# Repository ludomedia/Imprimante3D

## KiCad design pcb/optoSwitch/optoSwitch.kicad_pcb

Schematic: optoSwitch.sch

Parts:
IC1: OPTOSWITCH; DIP4F
K1: CONN_3
R1: 220R
R2: 4k7

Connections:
+5V: K1.1, R1.1, R2.1
GND: IC1.2, IC1.3, K1.3
unnamed: IC1.4, K1.2 (PM), R2.2
unnamed: IC1.1, R1.2

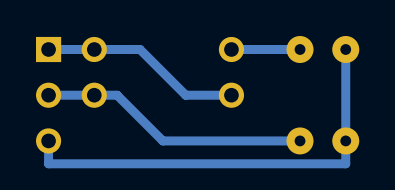
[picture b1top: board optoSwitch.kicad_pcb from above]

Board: 2 copper layers, 4 parts (0 on the bottom side), 4 nets.

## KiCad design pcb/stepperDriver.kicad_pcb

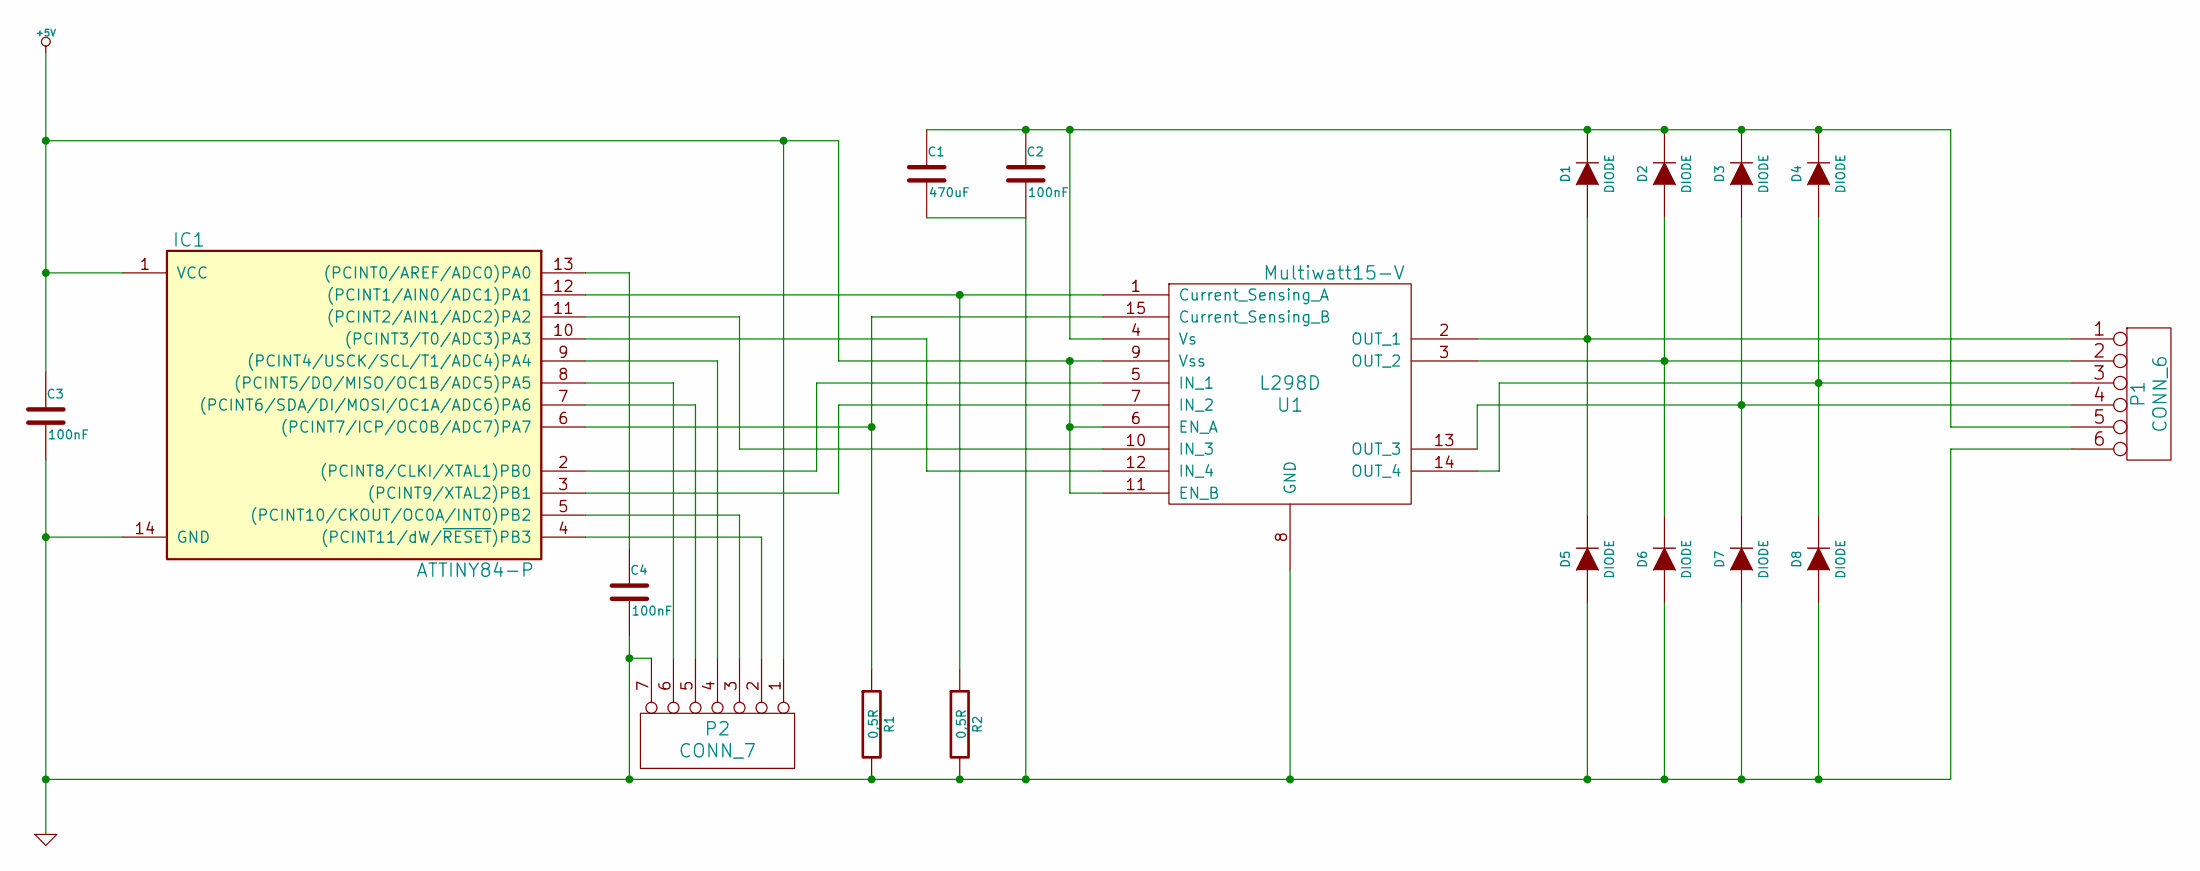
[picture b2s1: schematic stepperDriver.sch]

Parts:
C1: 470uF
C2, C3, C4: 100nF
D1, D2, D3, D4, D5, D6, D7, D8: DIODE
IC1: ATTINY84-P; DIP14
P1: CONN_6
P2: CONN_7
R1, R2: 0,5R
U1: L298D; Multiwatt15-V

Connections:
+5V: C3.1, IC1.1 (VCC), P2.1, U1.6 (EN_A), U1.9 (Vss), U1.11 (EN_B)
GND: C1.2, C2.2, C3.2, C4.2, D5.1 (A), D6.1 (A), D7.1 (A), D8.1 (A), IC1.14 (GND), P1.6, P2.7, R1.2, R2.2, U1.8 (GND)
unnamed: IC1.9 ((PCINT4/USCK/SCL/T1/ADC4)PA4), P2.4
unnamed: IC1.8 ((PCINT5/DO/MISO/OC1B/ADC5)PA5), P2.6
unnamed: D1.1 (A), D5.2 (K), P1.1, U1.2 (OUT_1)
unnamed: D2.1 (A), D6.2 (K), P1.2, U1.3 (OUT_2)
unnamed: D3.1 (A), D7.2 (K), P1.4, U1.13 (OUT_3)
unnamed: D4.1 (A), D8.2 (K), P1.3, U1.14 (OUT_4)
unnamed: C4.1, IC1.13 ((PCINT0/AREF/ADC0)PA0)
unnamed: IC1.7 ((PCINT6/SDA/DI/MOSI/OC1A/ADC6)PA6), P2.5
unnamed: IC1.4 ((PCINT11/dW/~RESET~)PB3), P2.2
unnamed: IC1.11 ((PCINT2/AIN1/ADC2)PA2), U1.10 (IN_3)
unnamed: IC1.5 ((PCINT10/CKOUT/OC0A/INT0)PB2), P2.3
unnamed: IC1.3 ((PCINT9/XTAL2)PB1), U1.7 (IN_2)
unnamed: IC1.2 ((PCINT8/CLKI/XTAL1)PB0), U1.5 (IN_1)
unnamed: IC1.10 ((PCINT3/T0/ADC3)PA3), U1.12 (IN_4)
unnamed: IC1.6 ((PCINT7/ICP/OC0B/ADC7)PA7), R1.1, U1.15 (Current_Sensing_B)
unnamed: IC1.12 ((PCINT1/AIN0/ADC1)PA1), R2.1, U1.1 (Current_Sensing_A)
unnamed: C1.1, C2.1, D1.2 (K), D2.2 (K), D3.2 (K), D4.2 (K), P1.5, U1.4 (Vs)

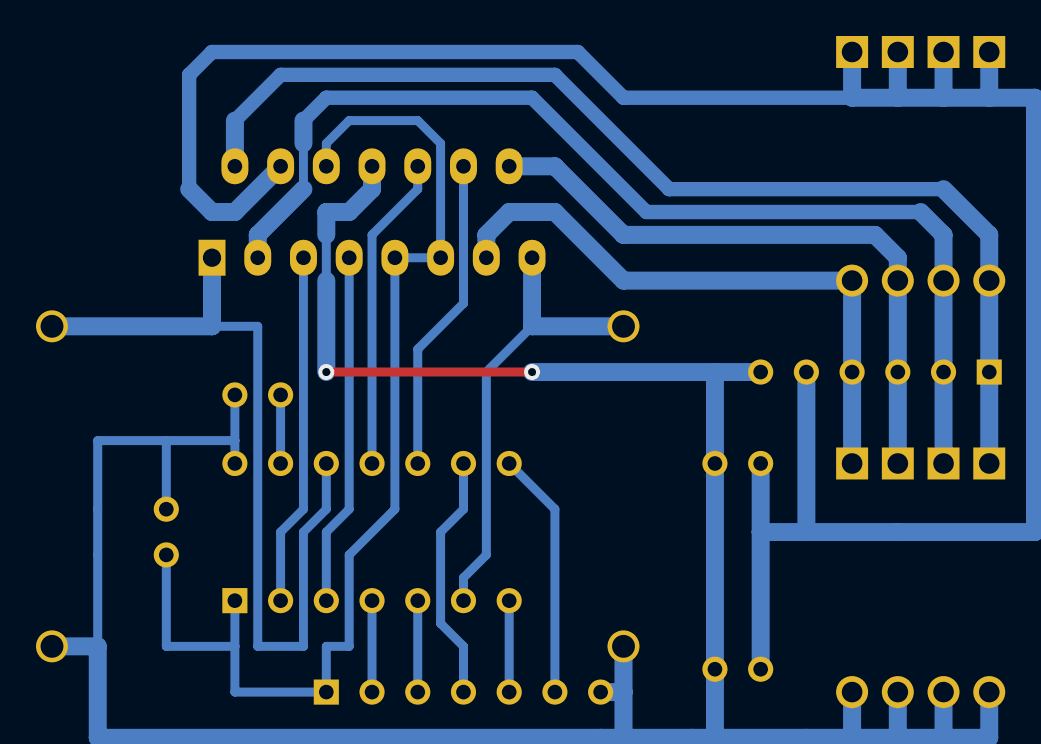
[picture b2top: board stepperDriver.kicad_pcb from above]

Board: 2 copper layers, 18 parts (0 on the bottom side), 19 nets.

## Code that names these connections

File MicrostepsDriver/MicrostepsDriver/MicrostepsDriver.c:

/*
 * MicrostepsDriver.c
 *
 * Created: 06.06.2013 19:50:59
 * Author: marc
 *
 *
 * -pattiny45 -P\\.\COM4 -b19200 -carduino -C"C:\$(Device)Program Files (x86)\arduino-1.0.4\hardware\tools\avr\etc/avrdude.conf" -v -v -Uflash:w:"$(ProjectDir)Debug\$(ItemFileName).hex":i
 * -p attiny45 -carduino -P\\.\COM4 -b19200 -U lfuse:w:0xE2:m -U hfuse:w:0xdf:m -C"C:\$(Device)Program Files (x86)\arduino-1.0.4\hardware\tools\avr\etc/avrdude.conf" -v -v
 *
 * -pattiny84 -P\\.\COM4 -b19200 -carduino -C"C:\$(Device)Program Files (x86)\arduino-1.0.4\hardware\tools\avr\etc/avrdude.conf" -v -v -Uflash:w:"$(ProjectDir)Debug\$(ItemFileName).hex":i
 * -pattiny84 -P\\.\COM4 -b19200 -carduino -U lfuse:w:0xE2:m -U hfuse:w:0xdf:m -C"C:\$(Device)Program Files (x86)\arduino-1.0.4\hardware\tools\avr\etc/avrdude.conf" -v -v
 *
 */ 

#include <avr/delay.h>
#include <avr/interrupt.h>
#include <avr/pgmspace.h>

// 1 A
const unsigned char sinewave[] PROGMEM = {
	0,  3,  5,  8, 11, 13, 16, 19, 21, 24, 26, 29, 32, 34, 37, 39,
	42, 44, 47, 49, 51, 54, 56, 58, 61, 63, 65, 67, 69, 71, 73, 75,
	77, 79, 81, 83, 84, 86, 88, 89, 91, 92, 93, 95, 96, 97, 98, 100,
	101, 102, 103, 103, 104, 105, 106, 106, 107, 107, 108, 108, 108, 109, 109, 109,
	109, 109, 109, 109, 108, 108, 108, 107, 107, 106, 106, 105, 104, 103, 103, 102,
	101, 100, 98, 97, 96, 95, 93, 92, 91, 89, 88, 86, 84, 83, 81, 79,
	77, 75, 73, 71, 69, 67, 65, 63, 61, 58, 56, 54, 51, 49, 47, 44,
	42, 39, 37, 34, 32, 29, 26, 24, 21, 19, 16, 13, 11,  8,  5,  3
};

// 0.5 A
/*
const unsigned char sinewave[] PROGMEM = {
	0,  1,  3,  4,  5,  7,  8,  9, 11, 12, 13, 15, 16, 17, 18, 20,
	21, 22, 23, 24, 26, 27, 28, 29, 30, 31, 32, 34, 35, 36, 37, 38,
	39, 39, 40, 41, 42, 43, 44, 45, 45, 46, 47, 47, 48, 49, 49, 50,
	50, 51, 51, 52, 52, 53, 53, 53, 53, 54, 54, 54, 54, 54, 54, 54,
	54, 54, 54, 54, 54, 54, 54, 54, 53, 53, 53, 53, 52, 52, 51, 51,
	50, 50, 49, 49, 48, 47, 47, 46, 45, 45, 44, 43, 42, 41, 40, 39,
	39, 38, 37, 36, 35, 34, 32, 31, 30, 29, 28, 27, 26, 24, 23, 22,
	21, 20, 18, 17, 16, 15, 13, 12, 11,  9,  8,  7,  5,  4,  3,  1
};
*/
/*
const uint8_t sinewave[] PROGMEM = {
	128,131,134,137,140,144,147,150,153,156,159,162,165,168,171,174,
	177,179,182,185,188,191,193,196,199,201,204,206,209,211,213,216,
	218,220,222,224,226,228,230,232,234,235,237,239,240,241,243,244,
	245,246,248,249,250,250,251,252,253,253,254,254,254,255,255,255,
	255,255,255,255,254,254,254,253,253,252,251,250,250,249,248,246,
	245,244,243,241,240,239,237,235,234,232,230,228,226,224,222,220,
	218,216,213,211,209,206,204,201,199,196,193,191,188,185,182,179,
	177,174,171,168,165,162,159,156,153,150,147,144,140,137,134,131,
	128,125,122,119,116,112,109,106,103,100, 97, 94, 91, 88, 85, 82,
	79, 77, 74, 71, 68, 65, 63, 60, 57, 55, 52, 50, 47, 45, 43, 40,
	38, 36, 34, 32, 30, 28, 26, 24, 22, 21, 19, 17, 16, 15, 13, 12,
	11, 10,  8,  7,  6,  6,  5,  4,  3,  3,  2,  2,  2,  1,  1,  1,
	1,  1,  1,  1,  2,  2,  2,  3,  3,  4,  5,  6,  6,  7,  8, 10,
	11, 12, 13, 15, 16, 17, 19, 21, 22, 24, 26, 28, 30, 32, 34, 36,
	38, 40, 43, 45, 47, 50, 52, 55, 57, 60, 63, 65, 68, 71, 74, 77,
	79, 82, 85, 88, 91, 94, 97,100,103,106,109,112,116,119,122,125
};
*/
#define COIL_B_DIR DDRB
#define COIL_A_PORT PORTB
#define COIL_A_PIN_1 PB0
#define COIL_A_PIN_2 PB1
#define COIL_A_RS PA1
#define COIL_A_RS_ADCMUX 0b000001

#define COIL_A_DIR DDRA
#define COIL_B_PORT PORTA
#define COIL_B_PIN_1 PA3
#define COIL_B_PIN_2 PA2
#define COIL_B_RS PA7
#define COIL_B_RS_ADCMUX 0b000111

#define DIRECTION_PORT PINA
#define DIRECTION_PIN PA6

#define STOP 0
#define UP 1
#define DOWN 2

unsigned char step_inc = 16;
unsigned char microstep = 0;
unsigned char divisor = 0;

/*
ISR(TIM0_OVF_vect)
{
	//PORTA ^= (1<<PA0);

	divisor++;
	divisor = divisor & 0x03;
	if(divisor==0) {
		if(steps>0) {
			microstep += step_inc;
			steps--;
		}			
		else if(steps<0) {
			microstep -= step_inc;
			steps++;
		}
		unsigned char i = microstep;
		OCR0A = pgm_read_byte_near(sinewave + i);
		i += 0x40;
		OCR0B = pgm_read_byte_near(sinewave + i);
	}
	COIL_A_PORT &= ~(1<<COIL_A_PIN_1);
	COIL_A_PORT |= (1<<COIL_A_PIN_2);
	COIL_B_PORT &= ~(1<<COIL_B_PIN_1);
	COIL_B_PORT |= (1<<COIL_B_PIN_2);
	
	//PORTA &= ~((1<<PA4)|(1<<PA2));
	//PORTA |= (1<<PA5)|(1<<PA3);
}

ISR(TIM0_COMPA_vect) {
	COIL_A_PORT |= (1<<COIL_A_PIN_1);
	COIL_A_PORT &= ~(1<<COIL_A_PIN_2);	
	//PORTA &= ~(1<<PA5);
	//PORTA |= (1<<PA4);
}

ISR(TIM0_COMPB_vect) {
	COIL_B_PORT |= (1<<COIL_B_PIN_1);
	COIL_B_PORT &= ~(1<<COIL_B_PIN_2);
	//PORTA &= ~(1<<PA3);
	//PORTA |= (1<<PA2);	
}

int main(void)
{
	//init_usart();
	OCR0A	=	0x40;		// PWM 1
	OCR0B	=	0x60;		// PWM 2
	//OCR0C	=	0xFF;
	
	//DDRB = 0xFF; //(1<<DDB5)|(1<<DDB4)|(0<<DDB3)|(0<<DDB2)|(1<<DDB1)|(0<<DDB0);
	//DDRA = 0xFF; //(1<<DDB5)|(1<<DDB4)|(0<<DDB3)|(0<<DDB2)|(1<<DDB1)|(0<<DDB0);
	COIL_A_DIR = (1<<COIL_A_PIN_1) | (1<<COIL_A_PIN_2);
	COIL_B_DIR = (1<<COIL_B_PIN_1) | (1<<COIL_B_PIN_2);

	DDRB &= ~(1<<PB2); // INT0 as entry
	MCUCR |= (1<<ISC01)|(1<<ISC00); // rising edge on INT0
	
	TCCR0A = (1<<COM0A1)|(0<<COM0A0)|(1<<COM0B1)|(0<<COM0B0)|(1<<WGM01)|(1<<WGM00);			// Fast PWM Non inverting mode TOP = 0xFF
	//TCCR0B = (0<<WGM02)|(0<<CS02)|(0<<CS01)|(1<<CS00);										// No prescaling
	TCCR0B = (0<<WGM02)|(0<<CS02)|(1<<CS01)|(0<<CS00);										// 8 prescaling
	TIMSK0 = (1<<TOIE0)|(1<<OCIE0A)|(1<<OCIE0B);											// Enable Timer 0 overflow interrupt
	
	sei();

	while(1) {
		if(GIFR & (1<<INTF0)) { // check if an interrupt request occured on INT0
		GIFR |= (1<<INTF0); // write one to clear the flag
		//steps++;
		if(DIRECTION_PORT & (1<<DIRECTION_PIN)) steps++;
		else steps--;
	}
}
*/
unsigned char analogRead() {
	ADCSRA |= (1<<ADSC); // Start conversion
	while(ADCSRA & (1<<ADSC)); // Wait end of conversion
	return ADCH;
}

#define COIL_A_FORWARD	COIL_A_PORT &= ~(1<<COIL_A_PIN_1); COIL_A_PORT |=  (1<<COIL_A_PIN_2)
#define COIL_A_OFF		COIL_A_PORT &= ~(1<<COIL_A_PIN_1); COIL_A_PORT &= ~(1<<COIL_A_PIN_2)
#define COIL_A_REVERSE	COIL_A_PORT |=  (1<<COIL_A_PIN_1); COIL_A_PORT &= ~(1<<COIL_A_PIN_2)

#define COIL_B_FORWARD	COIL_B_PORT &= ~(1<<COIL_B_PIN_1); COIL_B_PORT |=  (1<<COIL_B_PIN_2)
#define COIL_B_OFF		COIL_B_PORT &= ~(1<<COIL_B_PIN_1); COIL_B_PORT &= ~(1<<COIL_B_PIN_2)
#define COIL_B_REVERSE	COIL_B_PORT |=  (1<<COIL_B_PIN_1); COIL_B_PORT &= ~(1<<COIL_B_PIN_2)

#define SELECT_ADC_A ADMUX = (1<<REFS1)|(0<<REFS0)|COIL_A_RS_ADCMUX
#define SELECT_ADC_B ADMUX = (1<<REFS1)|(0<<REFS0)|COIL_B_RS_ADCMUX
#define START_CONVERSION ADCSRA |= (1<<ADSC);
#define WAIT_FOR_CONVERSION	while(ADCSRA & (1<<ADSC));

int main(void)
{
	COIL_A_DIR = (1<<COIL_A_PIN_1) | (1<<COIL_A_PIN_2);
	COIL_B_DIR = (1<<COIL_B_PIN_1) | (1<<COIL_B_PIN_2);

	DDRB &= ~(1<<PB2); // INT0 as entry
	MCUCR |= (1<<ISC01)|(1<<ISC00); // rising edge on INT0
			
	ADMUX = (1<<REFS1)|(0<<REFS0)|COIL_A_RS_ADCMUX; // Reference to 1.1V
	ADCSRA = (1<<ADEN)|(0<<ADPS2)|(1<<ADPS1)|(1<<ADPS0); // prescalar 8 (1MHz)
	ADCSRB = (1<<ADLAR); // Left alignement for reading ADCH only 
	DIDR0 = (1<<COIL_A_RS)|(1<<COIL_B_RS); // Reduce power consumption of unneeded digital inputs
	
	int cpt = 0;
	unsigned char dir;
	unsigned char voltage;
	signed char steps = 0;
	
    while(1) {

		/*cpt++;
		if(cpt==25) {
			cpt = 0;
			steps++;
		}
		*/
		
		if(GIFR & (1<<INTF0)) { // check if an interrupt request occured on INT0
			GIFR |= (1<<INTF0); // write one to clear the flag
			if(DIRECTION_PORT & (1<<DIRECTION_PIN)) steps++;
			else steps--;
		}				

		if(steps>0) {
			microstep += step_inc;
			steps--;
		}
		else if(steps<0) {
			microstep -= step_inc;
			steps++;
		}
		unsigned char i = microstep;
		
		SELECT_ADC_A;
		//_delay_us(50);
		START_CONVERSION;
		dir = i & 0x80;
		voltage = pgm_read_byte_near(sinewave + (i & 0x7F));
		WAIT_FOR_CONVERSION;
		if(ADCH<voltage) {
			if(dir) {
				COIL_A_FORWARD;
			}
			else {
				COIL_A_REVERSE;
			}
		}
		else {
			COIL_A_OFF;
		}		

		i += 0x40; // dephasage

		SELECT_ADC_B;
		//_delay_us(50);
		START_CONVERSION;
		dir = i & 0x80;
		voltage = pgm_read_byte_near(sinewave + (i & 0x7F));
		WAIT_FOR_CONVERSION;
		if(ADCH<voltage) {
			if(dir) {
				COIL_B_FORWARD;
			}
			else {
				COIL_B_REVERSE;
			}
		}
		else {
			COIL_B_OFF;
		}

/*				
		for(cpt=0;cpt<50;cpt++) {
			unsigned char v = analogRead();
			if(v<50) {
				COIL_A_FORWARD;
			}		
			else {
				COIL_A_OFF;
			}		
			_delay_us(100);
		}		

		COIL_A_OFF;
		_delay_ms(50);

		//COIL_B_FORWARD;
		//COIL_A_FORWARD;
		//_delay_ms(10);
		//COIL_B_OFF;
		//COIL_A_OFF;
		//_delay_ms(5);
*/
	}
}

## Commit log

2013-06-09 stepper driver pcb
2013-06-09 microstep driver
2013-06-09 cleanup
2013-06-11 axeXY
2013-06-11 boxed
2013-06-12 external drive test
2013-06-15 pcb capteur butée
2013-06-15 socle et tour
2013-06-17 group of pcb
2013-06-27 Correction résistance pullup
2013-06-30 added end step in tonokip firmware
2013-07-01 head-support
2013-07-06 current regulation with adc
2013-07-10 z support
2013-07-14 hotend
2013-07-14 test
2013-07-14 extruder
2013-07-15 modifs supports
2013-07-18 hotend support
2013-07-28 thermistor table
2013-09-01 xy-support
2013-09-18 end stops
2013-09-21 new extruder
2013-09-21 thermistor
2013-09-21 tonokip
2013-10-14 end-stop-z-support
2013-10-15 thermistor table generator for marlin
2013-10-17 vis pour mobile
2013-12-18 hotend new
2013-12-28 new extruder with fix
2013-12-30 position ressort
